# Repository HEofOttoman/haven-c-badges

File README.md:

# haven-c-badges
Badges for the Haven of artist & engineers

## Schematic

## BOM
The same as the jams guide.
|Item|Description|Cost|Link|
|---|---|---|---|
|KT-0805Y|Yellow SMD LED|||
|NT3H2111W0FHKH|NFC Chip|||
|CL10B224KA8NNNC|SMD Ceramic Capacitors|||
|0603WAF470JT5E|SMD Resistors|||

## Rationale
This will be a list of every design decision I made.

## Derivatives
This is what I used in the making of this project. ~~Also because I need to study calculus rn~~
- Jams.hackclub.com
- github.com/notaroomba/cybercard

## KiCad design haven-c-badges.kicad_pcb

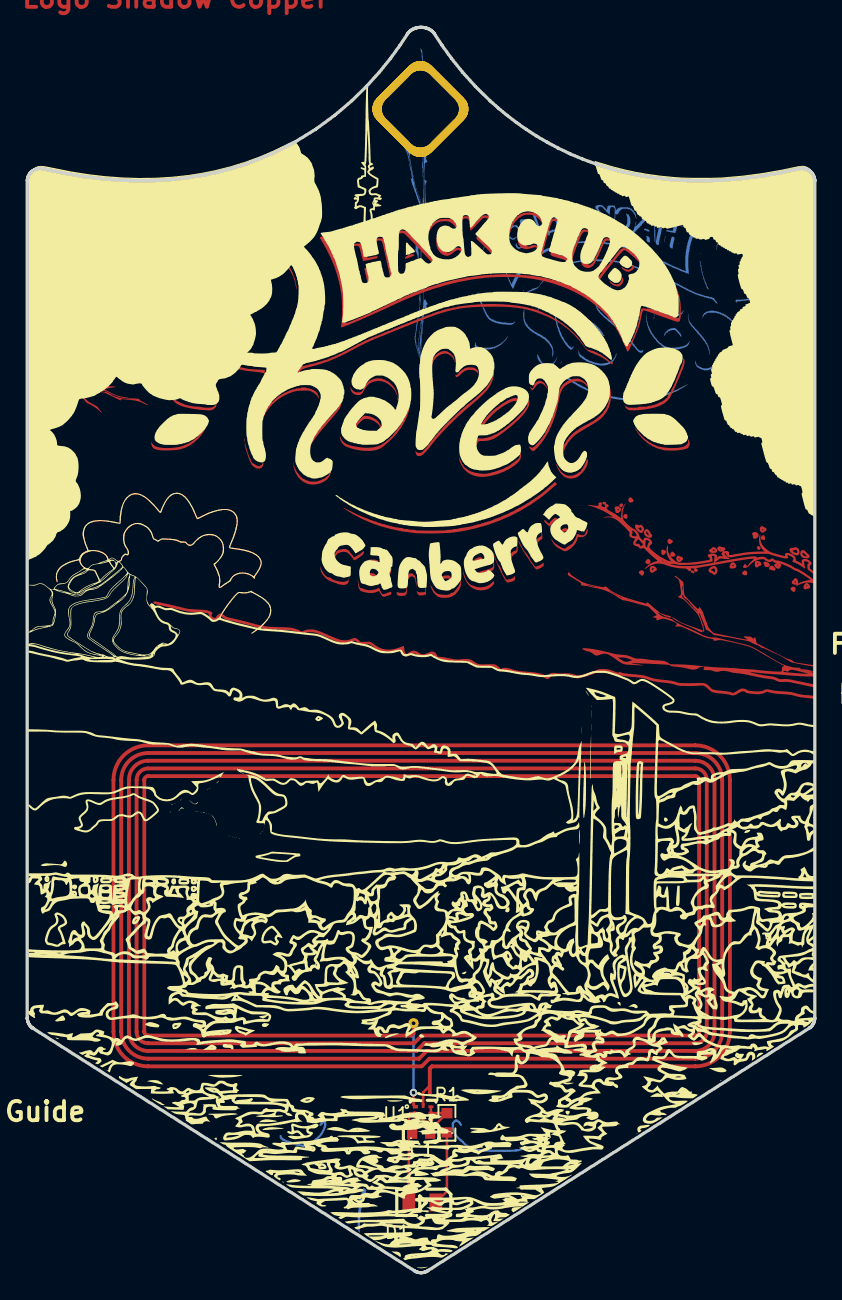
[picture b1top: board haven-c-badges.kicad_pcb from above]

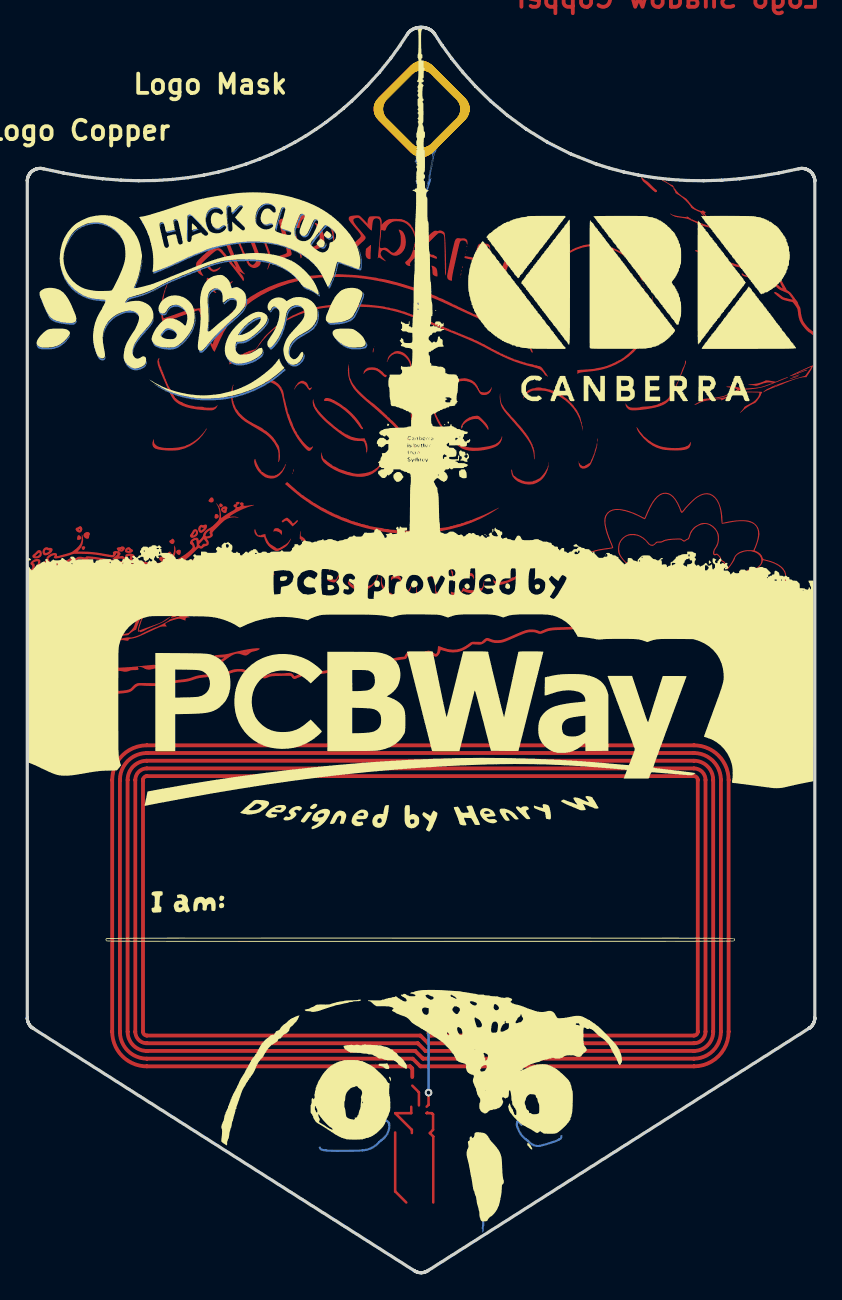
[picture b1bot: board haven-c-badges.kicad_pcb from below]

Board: 2 copper layers, 61.3 x 97.0 mm, 14 parts (3 on the bottom side), 5 nets.

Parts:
4mm Lanyard Hole: Lanyard_hole2
B.Silkscreen: LOGO
C1: 220nF; C0603
D1: LED; LED0805-R-RD
F.Cu, F.mask: LOGO
L1: 25X48MM_NFC_ANTENNA
Logo Copper: LOGO
Logo Mask: LOGO
Logo Shadow Copper: LOGO
LogoShadowMask: LOGO
R1: 47*; R0603
U1: NT3H2111W0FHKH; XQFN-8_L1.6-W1.6-P0.50-BL_NT3H2111W0FHKH
UV Print Silkscreen Guide: LOGO

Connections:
unnamed: D1.2 (A), R1.1
unnamed: C1.1, D1.1 (K), U1.2 (VSS)
unnamed: L1.P$2, U1.1 (LA)
unnamed: L1.P$1, U1.8 (LB)
unnamed: C1.2, R1.2, U1.6 (VCC), U1.7 (VOUT)
